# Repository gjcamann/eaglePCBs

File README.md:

eaglePCBs
=========

Collection of PCB Designs

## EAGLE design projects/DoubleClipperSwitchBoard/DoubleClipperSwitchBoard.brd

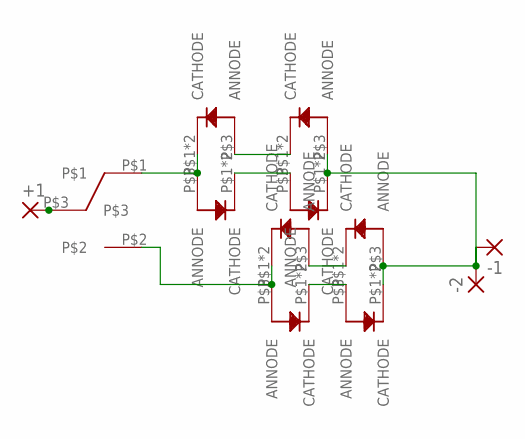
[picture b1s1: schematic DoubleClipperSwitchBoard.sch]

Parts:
+1: 2,15/1,0
-1, -2: 2,15/1,0
D1, D2, D3, D4: CLIPPER_BLOCK
U$1: SPDT_SOLDER
U$4, U$5, U$8, U$9: CLIPPER_BLOCK

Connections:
unnamed: +1.1, U$1.P$3
unnamed: U$4.P$3 (ANNODE), U$8.P$1 (CATHODE), U$8.P$2 (CATHODE)
unnamed: D1.P$3 (ANNODE), D2.P$1 (CATHODE), D2.P$2 (CATHODE), U$1.P$1
unnamed: D1.P$1 (CATHODE), D1.P$2 (CATHODE), D3.P$3 (ANNODE)
unnamed: U$1.P$2, U$4.P$1 (CATHODE), U$4.P$2 (CATHODE), U$5.P$3 (ANNODE)
unnamed: D2.P$3 (ANNODE), D4.P$1 (CATHODE), D4.P$2 (CATHODE)
unnamed: -1.1, -2.1, D3.P$1 (CATHODE), D3.P$2 (CATHODE), D4.P$3 (ANNODE), U$8.P$3 (ANNODE), U$9.P$1 (CATHODE), U$9.P$2 (CATHODE)
unnamed: U$5.P$1 (CATHODE), U$5.P$2 (CATHODE), U$9.P$3 (ANNODE)

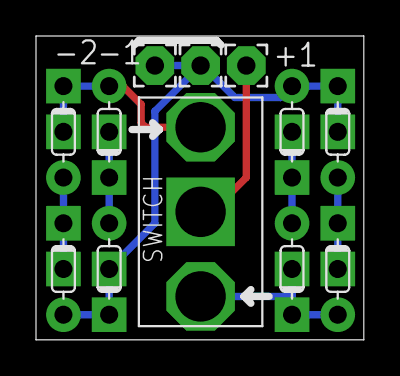
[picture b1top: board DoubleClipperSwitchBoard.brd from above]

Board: 2 copper layers, 18.2 x 16.9 mm, 12 parts (0 on the bottom side), 8 nets.

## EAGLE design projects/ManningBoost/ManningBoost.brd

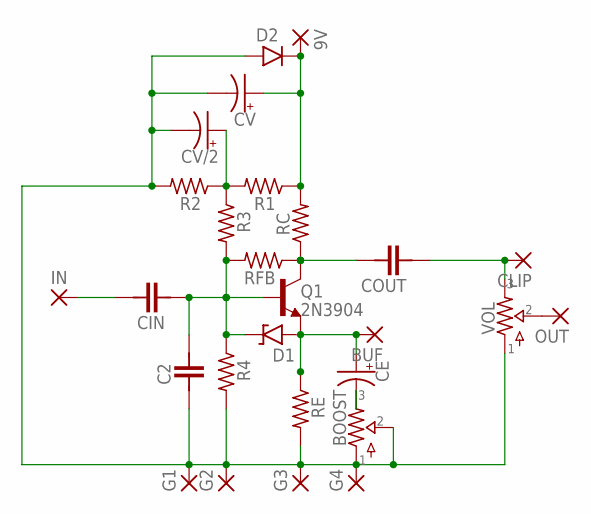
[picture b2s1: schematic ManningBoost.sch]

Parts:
9V: 2,15/1,0
BOOST: POTS; 16MM_CENTERMOUNT
BUF: 2,15/1,0
C2: CER/FILMBOX.1; BOX_SMALL
CE: 0631; 063_025
CIN: CER/FILMBOX.1; BOX_SMALL
CLIP: 2,15/1,0
COUT: CER/FILMBOX.1; BOX_SMALL
CV: 0631; 063_025
CV/2: 0631; 063_025
D1: ZENER.2; DO41-2
D2: DO41.2; DO41-2
G1, G2, G3, G4: 2,15/1,0
IN: 2,15/1,0
OUT: 2,15/1,0
Q1: 2N3904; TO92-
R1, R2, R3, R4: R_.3B; R0207/3
RC: R_.3B; R0207/3
RE: R_.3B; R0207/3
RFB: R_.3B; R0207/3
VOL: POTS16MM; 16MM

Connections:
$3: BOOST.1, BOOST.2, C2.2, CV.-, CV/2.-, D2.A, G1.1, G2.1, G3.1, G4.1, R2.2, R4.2, RE.2, VOL.1
unnamed: 9V.1, CV.+, D2.C, R1.1, RC.2
unnamed: COUT.1, Q1.1 (C), RC.1, RFB.1
unnamed: CV/2.+, R1.2, R2.1, R3.1
unnamed: BOOST.3, CE.-
unnamed: C2.1, CIN.2, D1.C, Q1.2 (B), R3.2, R4.1, RFB.2
unnamed: BUF.1, CE.+, D1.A, Q1.3 (E), RE.1
unnamed: CIN.1, IN.1
unnamed: OUT.1, VOL.2
unnamed: CLIP.1, COUT.2, VOL.3

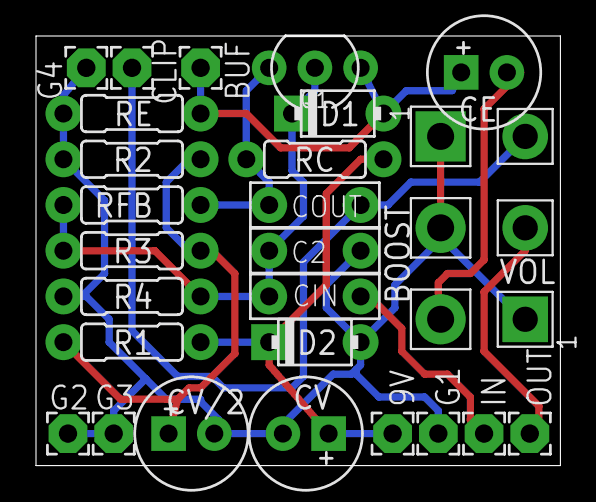
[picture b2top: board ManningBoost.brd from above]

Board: 2 copper layers, 29.1 x 23.9 mm, 27 parts (0 on the bottom side), 10 nets.

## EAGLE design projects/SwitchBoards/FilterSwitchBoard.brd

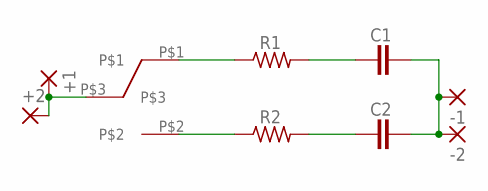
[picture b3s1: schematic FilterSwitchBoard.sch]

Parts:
+1, +2: 2,15/1,0
-1, -2: 2,15/1,0
C1, C2: CER/FILMBOX.1; BOX_SMALL
R1, R2: R_.3B; R0207/3
U$1: SPDT_SOLDER

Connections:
unnamed: R1.1, U$1.P$1
unnamed: C1.2, R1.2
unnamed: C2.2, R2.2
unnamed: R2.1, U$1.P$2
unnamed: -1.1, -2.1, C1.1, C2.1
unnamed: +1.1, +2.1, U$1.P$3

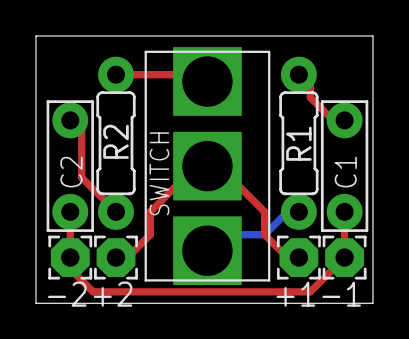
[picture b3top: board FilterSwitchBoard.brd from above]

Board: 2 copper layers, 18.7 x 14.8 mm, 9 parts (0 on the bottom side), 6 nets.

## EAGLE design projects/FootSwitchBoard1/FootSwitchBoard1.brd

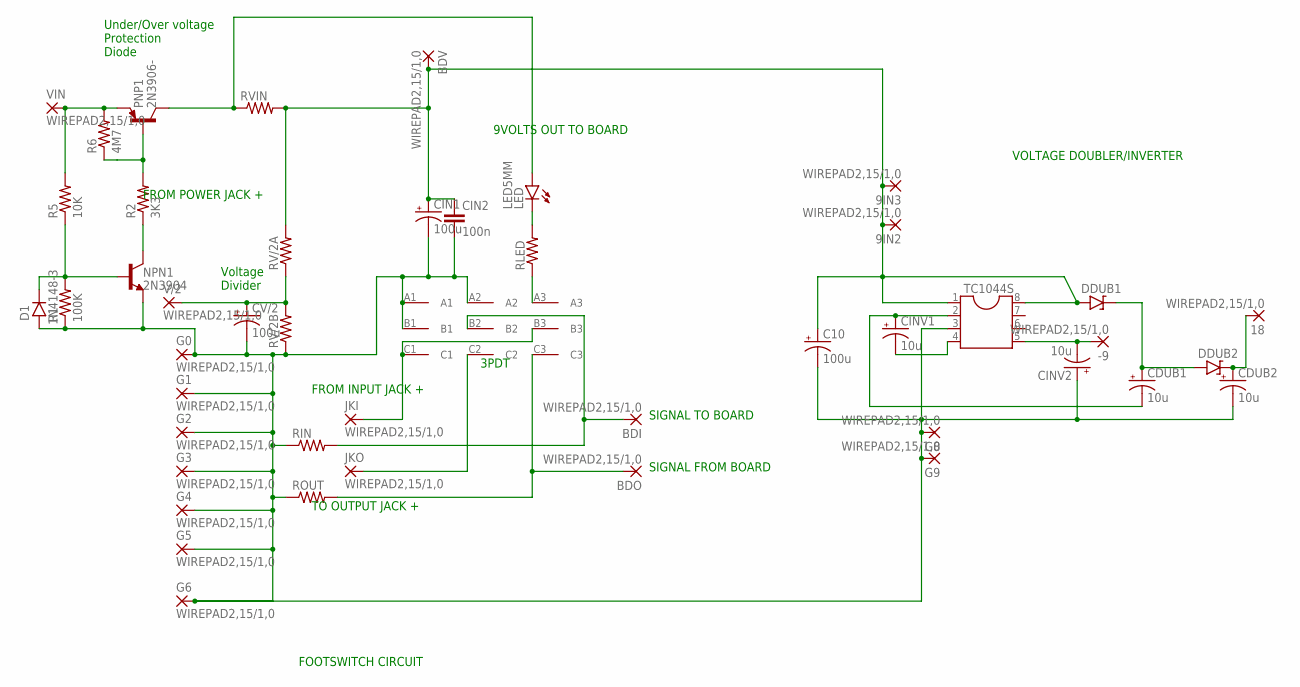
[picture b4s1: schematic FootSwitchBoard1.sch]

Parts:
9IN2, 9IN3, 18: WIREPAD2,15/1,0; 2,15/1,0
-9: WIREPAD2,15/1,0; 2,15/1,0
BDI: WIREPAD2,15/1,0; 2,15/1,0
BDO: WIREPAD2,15/1,0; 2,15/1,0
BDV: WIREPAD2,15/1,0; 2,15/1,0
C10: 100u; 080_035
CDUB1, CDUB2: 10u; 050_020_1
CIN1: 100u; 080_035
CIN2: 100n; 072X035
CINV1, CINV2: 10u; 050_020_1
CV/2: 100u; 080_035
D1: 1N4148-3; DO35-3
DDUB1, DDUB2: 1N47XX3; DO41-3
G0, G1, G2, G3, G4, G5, G6, G8, G9: WIREPAD2,15/1,0; 2,15/1,0
JKI: WIREPAD2,15/1,0; 2,15/1,0
JKO: WIREPAD2,15/1,0; 2,15/1,0
LED: LED5MM
NPN1: 2N3904; TO92-
PNP1: 2N3906-; TO92-
R1: 100K; R0207/3
R2: 3K3; R0207/3
R5: 10K; R0207/3
R6: 4M7; R0207/3
RIN: 6MM.2; R0207/2V
RLED: 6MM.3; R0207/3
ROUT: 6MM.2; R0207/2V
RV/2A, RV/2B: 6MM.3; R0207/3
RVIN: 6MM.3; R0207/3
TC1044S: DIL8; DIL08
U$1: SF17010F-0302; ALPHA_SF17010F-0302
V/2: WIREPAD2,15/1,0; 2,15/1,0
VIN: WIREPAD2,15/1,0; 2,15/1,0

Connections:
9INDUBINV: 9IN2.1, 9IN3.1, BDV.1, C10.+, CIN1.+, CIN2.1, DDUB1.A, RV/2A.2, RVIN.2, TC1044S.1, TC1044S.8
DDUB2: CDUB1.+, DDUB1.C, DDUB2.A
GDUBINV: C10.-, CDUB2.-, CIN1.-, CIN2.2, CINV2.+, CV/2.-, D1.A, G0.1, G1.1, G2.1, G3.1, G4.1, G5.1, G6.1, G8.1, G9.1, NPN1.3 (E), R1.1, RIN.1, ROUT.1, RV/2B.1, TC1044S.3, U$1.A1, U$1.A2, U$1.B1
unnamed: JKI.1, U$1.B3, U$1.C1
unnamed: JKO.1, U$1.C2
unnamed: LED.A, PNP1.1 (C), RVIN.1
unnamed: LED.K (C), RLED.2
unnamed: RLED.1, U$1.A3
unnamed: PNP1.2 (B), R2.2, R6.1
unnamed: BDI.1, RIN.2, U$1.B2
unnamed: NPN1.1 (C), R2.1
unnamed: CV/2.+, RV/2A.1, RV/2B.2, V/2.1
unnamed: BDO.1, ROUT.2, U$1.C3
unnamed: CDUB1.-, CINV1.+, TC1044S.2
unnamed: D1.C, NPN1.2 (B), R1.2, R5.1
unnamed: CINV1.-, TC1044S.4
unnamed: -9.1, CINV2.-, TC1044S.5
unnamed: 18.1, CDUB2.+, DDUB2.C
unnamed: PNP1.3 (E), R5.2, R6.2, VIN.1

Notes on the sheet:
Under/Over voltage Protection Diode
3PDT
Voltage Divider
9VOLTS OUT TO BOARD
FROM INPUT JACK +
TO OUTPUT JACK +
SIGNAL TO BOARD
SIGNAL FROM BOARD
FOOTSWITCH CIRCUIT
VOLTAGE DOUBLER/INVERTER
FROM POWER JACK +

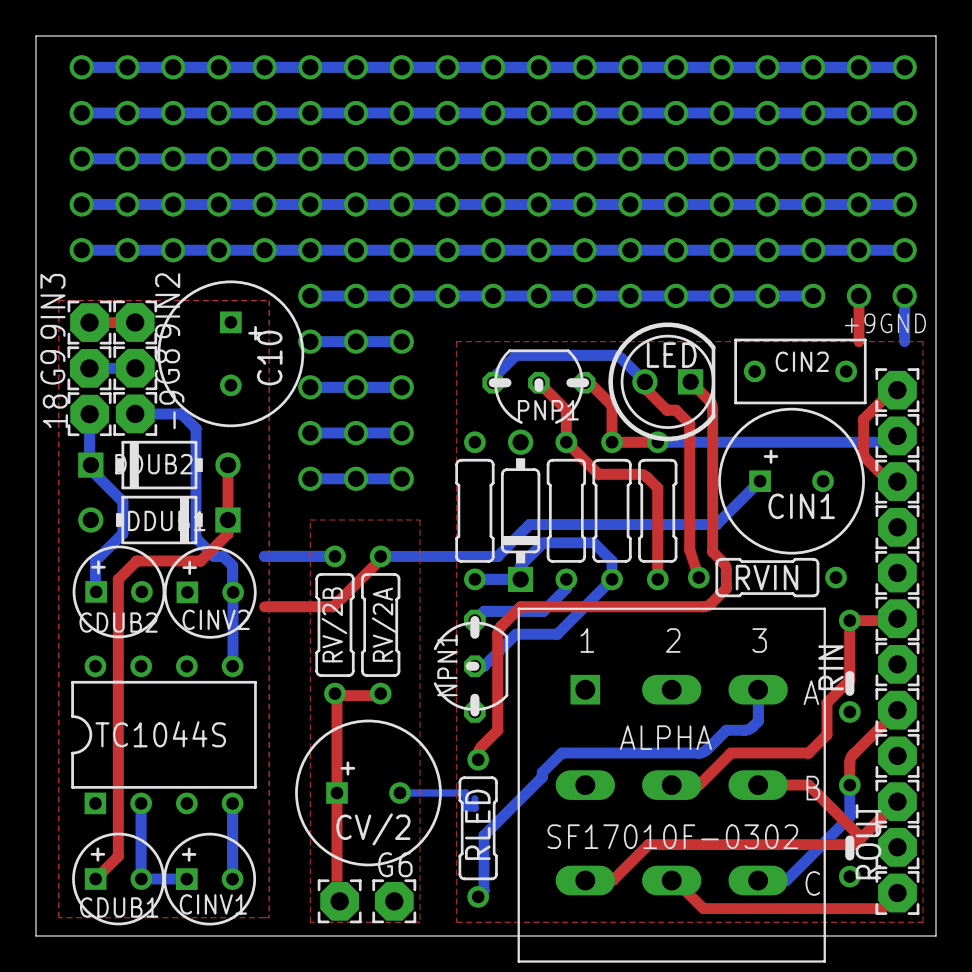
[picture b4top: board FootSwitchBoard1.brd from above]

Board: 2 copper layers, 50.0 x 50.0 mm, 46 parts (0 on the bottom side), 19 nets.

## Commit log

2013-07-10 Added initial set of libraries.
2013-07-10 Added FootSwitchBoard1 Schematic.
2013-07-10 Added gitignore for this project.
2013-07-11 Board updates.
2013-07-11 Ignore backup files.
2013-07-13 Board layout in progress.
2013-07-13 Added ITEAD design files.
2013-07-16 Added sparkfun rules.
2013-07-16 Implemented combined inverter/doubler board.
2013-07-25 Exclude LTSpice files.
2013-07-25 Circuit mods, new OVP UVP circuit added.
2013-07-25 Added LT spice schematic for overvoltage protection and undervoltage protection.
2013-08-03 Library updates.
2013-08-03 Work in progress, switching back to reverse polarity protection only.
2013-08-03 Good layout with reverse polarity protection.
2013-08-08 Finalized layout with ground and power planes.
2013-08-08 Added prototype area.
2013-08-10 Final version of files.
2013-08-10 Add modded CAM, include values on silkscreen
2013-08-10 Add CAM files from project.
2013-12-19 Added Madbean Pedal libraries.
2014-02-03 Move gust markof libraries to own folder
2014-02-03 Move madpeab parts to own folder.
2014-02-03 Rename my own pedal parts library.
2014-02-03 Updated madbean pedal parts.
2014-02-03 Added solder switch part.
2014-02-03 Remove library - see gc_pedal_parts.lbr now.
2014-02-03 Added FilterSwitchBoard project.
2014-02-03 Added clipper boards, filter board update.
2014-02-03 Updated switch part, added clipper part.
2014-02-03 Added OSHPark Design Rule Check file.
2014-02-03 Pass OSHPark DRC.
2014-02-04 Updated libraries to have symbols that on 0.1inch pin spacing.
2014-02-04 Initial version of Manning boost.
2014-02-11 Ignore gerber files.
2014-02-11 Update description.
2014-02-11 Add OSHParm CAM job.
2014-02-11 Update clipper diodes to print on both sides of paper.
2014-02-11 Final project updates. Ready to send to oshpark.
2014-02-11 Moved switchboard projects into their own folders.
2014-02-13 Updated clipper symbol to include diode.
2014-02-13 Updated to use new clipper block.
2014-02-13 Added documentation.

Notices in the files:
projects/DoubleClipperSwitchBoard/DoubleClipperSwitchBoard.brd:
GJCAMANN(C)2014
